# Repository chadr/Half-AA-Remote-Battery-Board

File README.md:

# Half AA Remote Battery Board
 Remote battery board for vintage computers.

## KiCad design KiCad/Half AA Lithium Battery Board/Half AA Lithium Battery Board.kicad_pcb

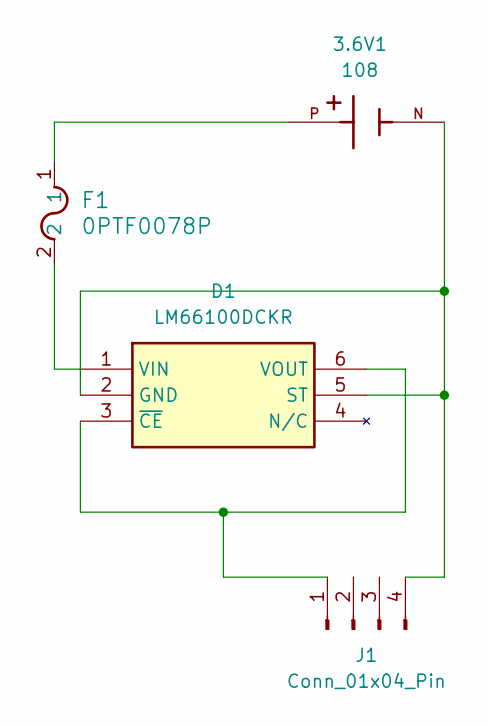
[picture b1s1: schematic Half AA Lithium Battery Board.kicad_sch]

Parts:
3.6V1: 108; BAT_108; PARTREV E
D1: LM66100DCKR; SOP65P210X110-6N; Manufacturer_Part_Number LM66100DCKR; Mouser Part Number 595-LM66100DCKR
F1: 0PTF0078P; FUSE_0PTF0078P_LTF
J1: Conn_01x04_Pin; PinHeader_1x04_P2.54mm_Vertical

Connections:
unnamed: 3.6V1.P, F1.1
unnamed: 3.6V1.N, D1.2 (GND), D1.5 (ST), J1.4
unnamed: D1.1 (VIN), F1.2
unnamed: D1.3 (~CE), D1.6 (VOUT), J1.1

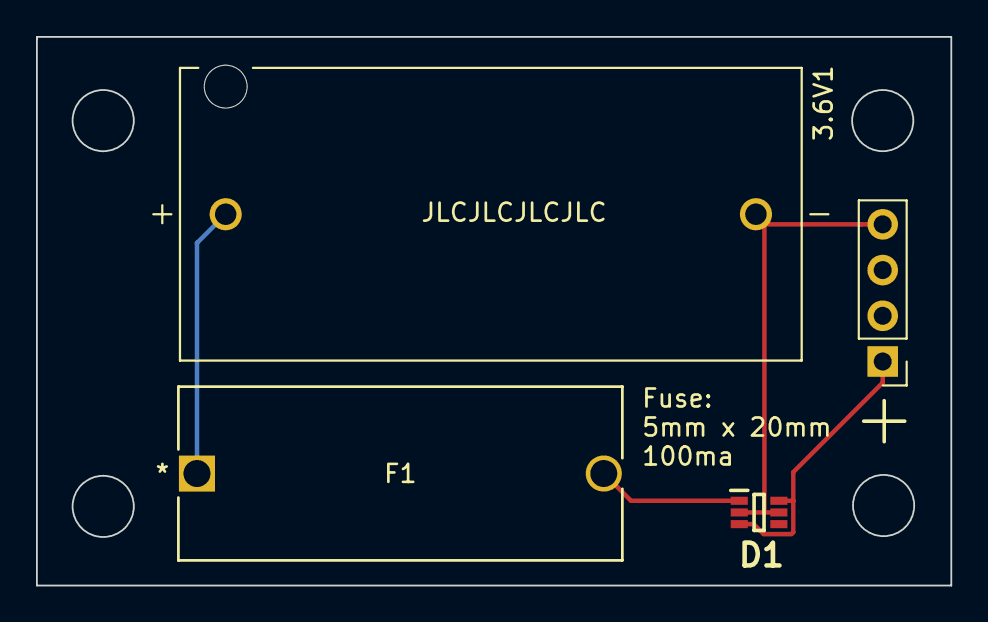
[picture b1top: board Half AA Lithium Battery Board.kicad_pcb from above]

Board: 2 copper layers, 50.8 x 30.5 mm, 4 parts (0 on the bottom side), 4 nets.

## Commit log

2023-11-25 Update diode
2023-12-19 add ideal diode
    replace traditional diode with ideal diode chip
